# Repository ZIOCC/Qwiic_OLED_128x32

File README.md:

# Zio Qwiic OLED Display (0.91", 128x32 pixels)

> This product can be available for purchase [here](https://www.smart-prototyping.com/Zio-OLED-Display-0-91-in-128-32-Qwiic.html).

#### Description

This Zio OLED Display features a whopping 128x32 pixels in a small 0.91” (diagonal) frame. That’s 4,000 itsy-bitsy LEDs. [pause for effect]

Speed isn’t compromised however, thanks to its I2C command structure. Your firmware only needs to send the changes that it wants to make, rather than transferring information for every single pixel during each screen update.

As an OLED, it comes with all the perks of being able to emit light (unlike LCDs). No backlight layer here! Therefore, it’s thinner, consumes less power, and has higher contrast. With this size, it can display up to 3 lines of text.

The breakout board also features 4 mounting holes that can be snapped off and 2 Qwiic connectors to allow for quick and easy daisy-chaining.

> Note: As with all of the Version 1.0 Zio Qwiic boards, this board has been produced with the I2C pull-ups disconnected by default. If there's a significant length of wire between this board and your MCU, you'll need to solder closed the solder jumpers (labeled SDA, 3v3 and SCL) to connect the pull-up resistors to VCC.

#### Specification

* Communication Protocols: I2C
* IC: SSD1306
* I2C address: 0x3C
* Dimensions with Mounting  Tab: 25.1x 50.3mm
* Dimension without Mounting  Tab: 50.3x15.1mm
* Weight: 5g

#### Links

* [Adafruit GFX Library](https://github.com/adafruit/Adafruit-GFX-Library)
* [Adafruit SSD1306 Library](https://github.com/adafruit/Adafruit_SSD1306)
* [Demo Code](https://github.com/adafruit/Adafruit_SSD1306/tree/master/examples/ssd1306_128x32_i2c)
* [Eagle files](https://github.com/ZIOCC/Qwiic_OLED_128x32)

> ###### About Zio
> Zio is a new line of open sourced, compact, and grid layout boards, fully integrated for Arduino and Qwiic ecosystem. Designed ideally for wearables, robotics, small-space limitations or other on the go projects. Check out other awesome Zio products [here](https://www.smart-prototyping.com/Zio).

> All Zio products are released under the [Creative Commons Attribution, Share-Alike License](https://creativecommons.org/licenses/by-sa/4.0/), and in accordance with the principles of the [Open Source Hardware Association's OSHW Statement of Principles 1.0 and OSHW Definition 1.0](https://www.oshwa.org/definition/).

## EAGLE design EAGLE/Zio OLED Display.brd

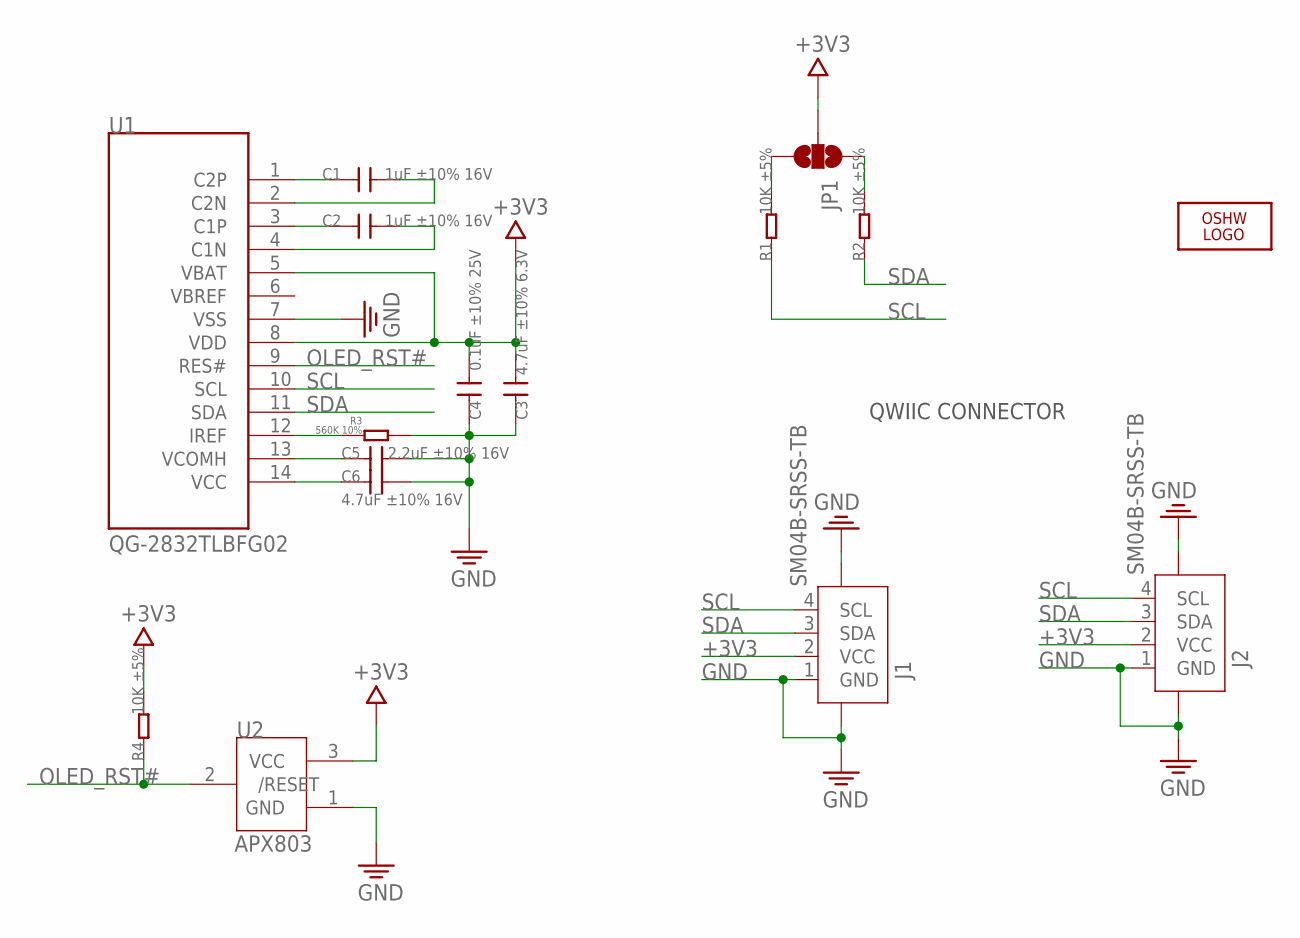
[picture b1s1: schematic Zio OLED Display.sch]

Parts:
C1, C2: 1uF ±10% 16V; 0603
C3: 4.7uF ±10% 6.3V; 0603
C4: 0.1uF ±10% 25V; 0603
C5: 2.2uF ±10% 16V; 0603
C6: 4.7uF ±10% 16V; 0603
J1, J2: SM04B-SRSS-TB; JST-SH-4P
JP1: JUMPER-SMT_3_2-NC_PASTE_NOCREM; SMT-JUMPER_3_2-NC_PASTE_SILK_NOCREM
LOGO1: LOGO-OSHW-6MILX0070-NT; OSHW_6X70_NOTEXT
R1, R2, R4: 10K ±5%; 0603
R3: 560K 10%; 0603
U1: QG-2832TLBFG02; OLED-12832
U2: APX803; SOT23

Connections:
+3V3: C3.1, C4.1, J1.2 (VCC), J2.2 (VCC), JP1.2, R4.2, U1.5 (VBAT), U1.8 (VDD), U2.3 (VCC)
GND: C3.2, C4.2, C5.2, C6.2, J1.1 (GND), J1.NC1 (5), J1.NC2 (6), J2.1 (GND), J2.NC1 (5), J2.NC2 (6), R3.1, U1.7 (VSS), U2.1 (GND)
unnamed: C1.2, U1.1 (C2P)
unnamed: C1.1, U1.2 (C2N)
unnamed: C2.2, U1.3 (C1P)
unnamed: C2.1, U1.4 (C1N)
unnamed: JP1.3, R1.2
unnamed: C5.1, U1.13 (VCOMH)
unnamed: C6.1, U1.14 (VCC)
unnamed: JP1.1, R2.2
unnamed: R3.2, U1.12 (IREF)
OLED_RST#: R4.1, U1.9 (RES#), U2.2 (/RESET)
SCL: J1.4 (SCL), J2.4 (SCL), R1.1, U1.10 (SCL)
SDA: J1.3 (SDA), J2.3 (SDA), R2.1, U1.11 (SDA)

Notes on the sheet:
QWIIC CONNECTOR

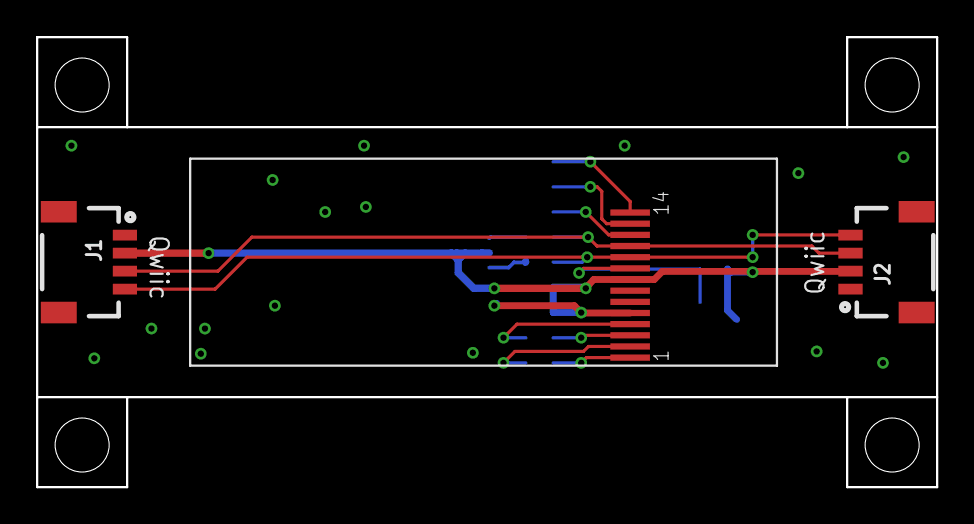
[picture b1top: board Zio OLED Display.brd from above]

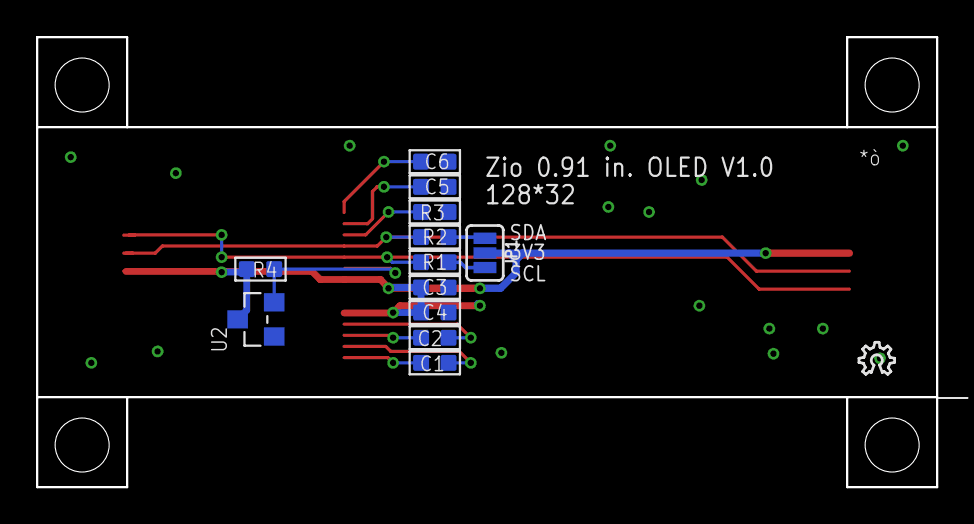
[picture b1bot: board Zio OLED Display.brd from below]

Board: 2 copper layers, 50.0 x 25.0 mm, 18 parts (14 on the bottom side), 14 nets.

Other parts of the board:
E$10: 7MM
U$3: 6MM
